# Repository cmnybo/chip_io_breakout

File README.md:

# C.H.I.P. GPIO Breakout

This is a breakout that attaches to the LCD Adapter board with a 34 pin ribbon cable and IDC connectors.

## Features

* 2 I2C headers
* 6 SPI headers
* 16 pin GPIO header
* 16 pin analog header
* 12 bit 8 channel ADC (MAX11629)
* 12 bit 2 channel DAC (MAX5702)
* Buffered voltage reference output (2.048V & 2.5V)
* External reference voltage input (1.24V - 3.3V)
* Filtered analog power supply.

The original design files for this board were created in [KiCAD](http://kicad-pcb.org/). <br/>
There are PDF copies of the schematic, PCB layout, and bill of materials in the "pdf" directory.<br/>
The "gerber" directory contains all of the files needed to have some boards made.<br/>
The device tree overlay and example python program are in the "source" directory.

</img>

## Pinouts
</img>

## License
**This project is open source hardware.**

The hardware design files are licensed under a [Creative Commons Attribution-ShareAlike](https://creativecommons.org/licenses/by-sa/3.0) license.
</img>

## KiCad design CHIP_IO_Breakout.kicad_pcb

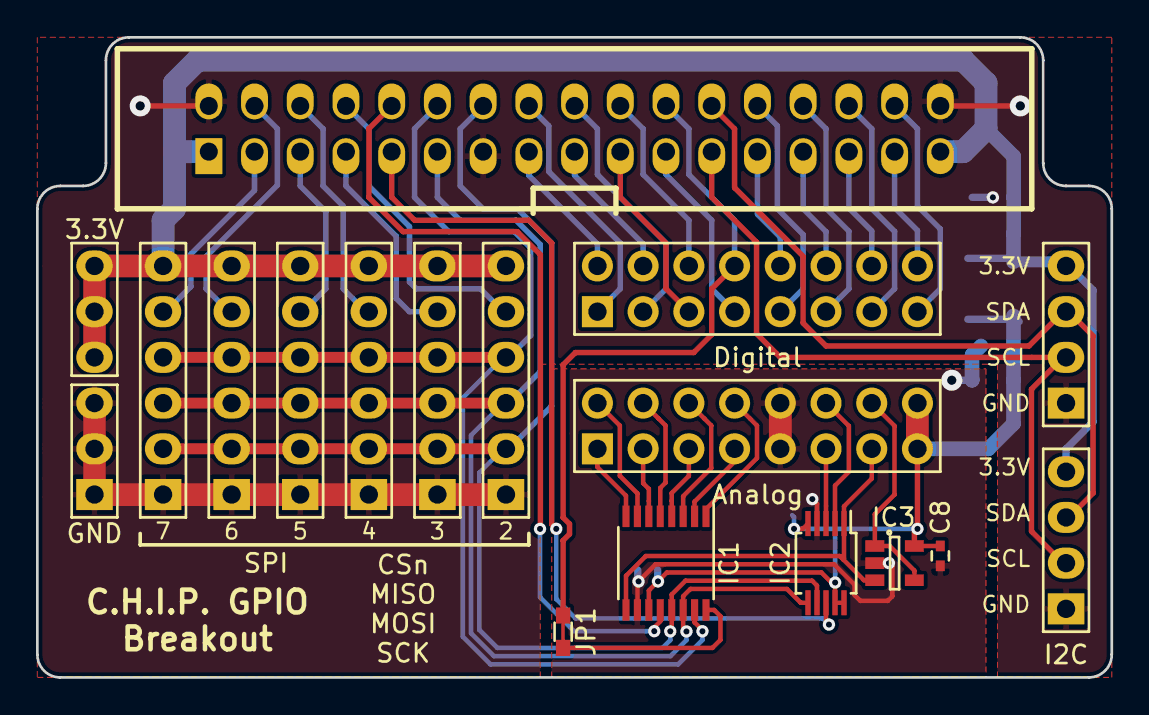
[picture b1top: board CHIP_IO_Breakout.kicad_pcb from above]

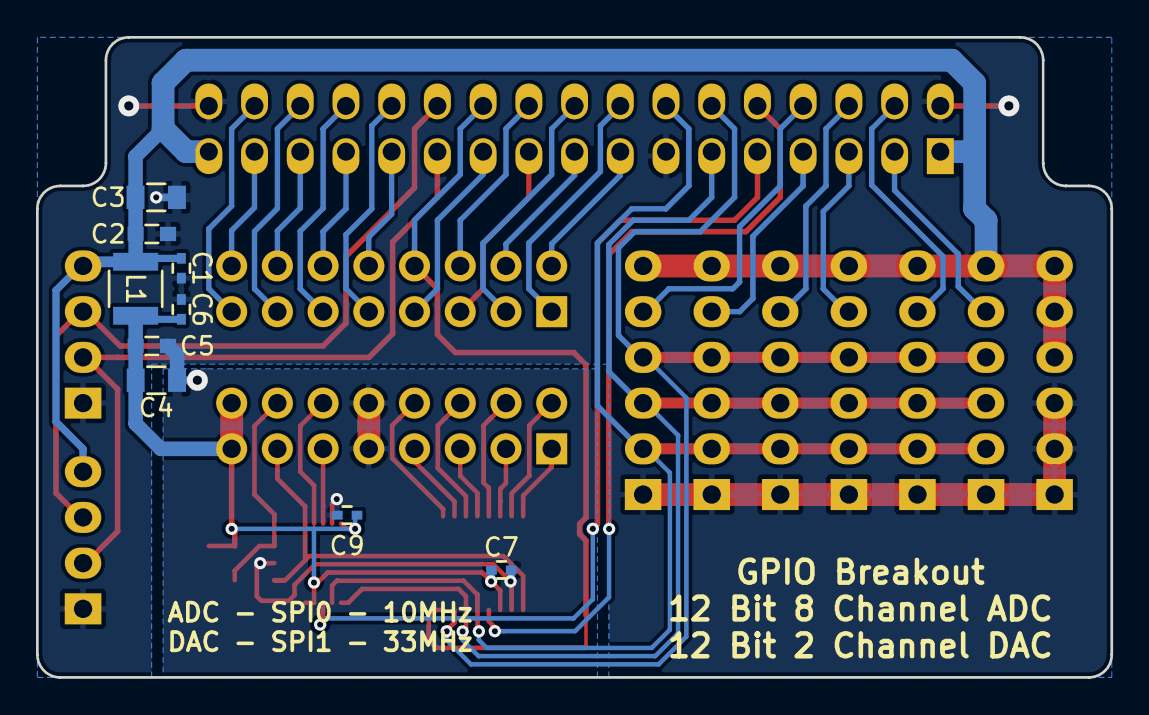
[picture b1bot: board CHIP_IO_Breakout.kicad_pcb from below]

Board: 2 copper layers, 59.7 x 35.6 mm, 26 parts (9 on the bottom side), 44 nets.

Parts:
C1, C6, C7, C8, C9: 0.1µF; C_0402
C2, C5: 1µF; C_0603
C3, C4: 10µF; C_0805
IC1: MAX11629; SSOP-16_3.9x4.9mm_Pitch0.635mm
IC2: MAX5702; MSOP-10_3x3mm_Pitch0.5mm
IC3: MCP6L01; SOT-23-5
JP1: Jumper_NC_Small; R_0603
L1: 100µH; C_1210
P1: Digital; Pin_Header_Straight_2x08
P2: Analog; Pin_Header_Straight_2x08
P3, P5: I2C; Pin_Header_Straight_1x04
P7: SPI2; Pin_Header_Straight_1x06
P8: SPI3; Pin_Header_Straight_1x06
P9: SPI4; Pin_Header_Straight_1x06
P10: SPI5; Pin_Header_Straight_1x06
P11: SPI6; Pin_Header_Straight_1x06
P12: SPI7; Pin_Header_Straight_1x06
P13: GPIO; vasch_strip_17x2
P14: Power; Pin_Header_Straight_1x06

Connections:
+3.3VADC: C4.1, C5.1, C6.1, C7.1, C8.1, C9.1, IC1.11, IC2.5, IC2.9, IC2.10, IC3.5, L1.2, P2.15, P2.16
+3V3: C1.1, C2.1, C3.1, L1.1, P3.4, P5.4, P7.6, P8.6, P9.6, P10.6, P11.6, P12.6, P13.1, P13.33, P14.4, P14.5, P14.6
/ADC0: IC1.1, P2.8
/ADC1: IC1.2, P2.7
/ADC2: IC1.3, P2.6
/ADC3: IC1.4, P2.5
/ADC4: IC1.5, P2.4
/ADC5: IC1.6, P2.3
/ADC6: IC1.7, P2.2
/ADC7: IC1.8, P2.1
/CS0: IC1.12, P13.10
/CS1: IC2.8, P13.9
/CS2: P7.5, P13.8
/CS3: P8.5, P13.7
/CS4: P9.5, P13.6
/CS5: P10.5, P13.5
/CS6: P11.5, P13.4
/CS7: P12.5, P13.3
/DAC0: IC2.2, P2.12
/DAC1: IC2.3, P2.11
/INT1: IC1.16, JP1.1, JP1.2, P1.8, P13.22
/INT3: P1.7, P13.21
/IO0: P1.10, P13.25
/IO1: P1.9, P13.26
/IO2: P1.12, P13.27
/IO3: P1.11, P13.28
/IO4: P1.14, P13.29
/IO5: P1.13, P13.30
/IO6: P1.16, P13.31
/IO7: P1.15, P13.32
/MISO: IC1.15, P7.4, P8.4, P9.4, P10.4, P11.4, P12.4, P13.12
/MOSI: IC1.14, IC2.6, P7.3, P8.3, P9.3, P10.3, P11.3, P12.3, P13.11
/PWM: P1.5, P13.19
/Ref: IC1.9, IC2.1, IC3.3, P2.13
/RefO: IC3.1, IC3.4, P2.14
/SCK: IC1.13, IC2.7, P7.2, P8.2, P9.2, P10.2, P11.2, P12.2, P13.14
/SCL2: P3.2, P5.2, P13.23
/SDA2: P3.3, P5.3, P13.24
/XIO3: P1.2, P13.15
/XIO4: P1.1, P13.16
/XIO5: P1.4, P13.17
/XIO6: P1.3, P13.18
/XIO7: P1.6, P13.20
GND: C1.2, C2.2, C3.2, C4.2, C5.2, C6.2, C7.2, C8.2, C9.2, IC1.10, IC2.4, IC3.2, P2.9, P2.10, P3.1, P5.1, P7.1, P8.1, P9.1, P10.1, P11.1, P12.1, P13.2, P13.13, P13.34, P14.1, P14.2, P14.3

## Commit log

2016-10-17 Updated schematic PDF
